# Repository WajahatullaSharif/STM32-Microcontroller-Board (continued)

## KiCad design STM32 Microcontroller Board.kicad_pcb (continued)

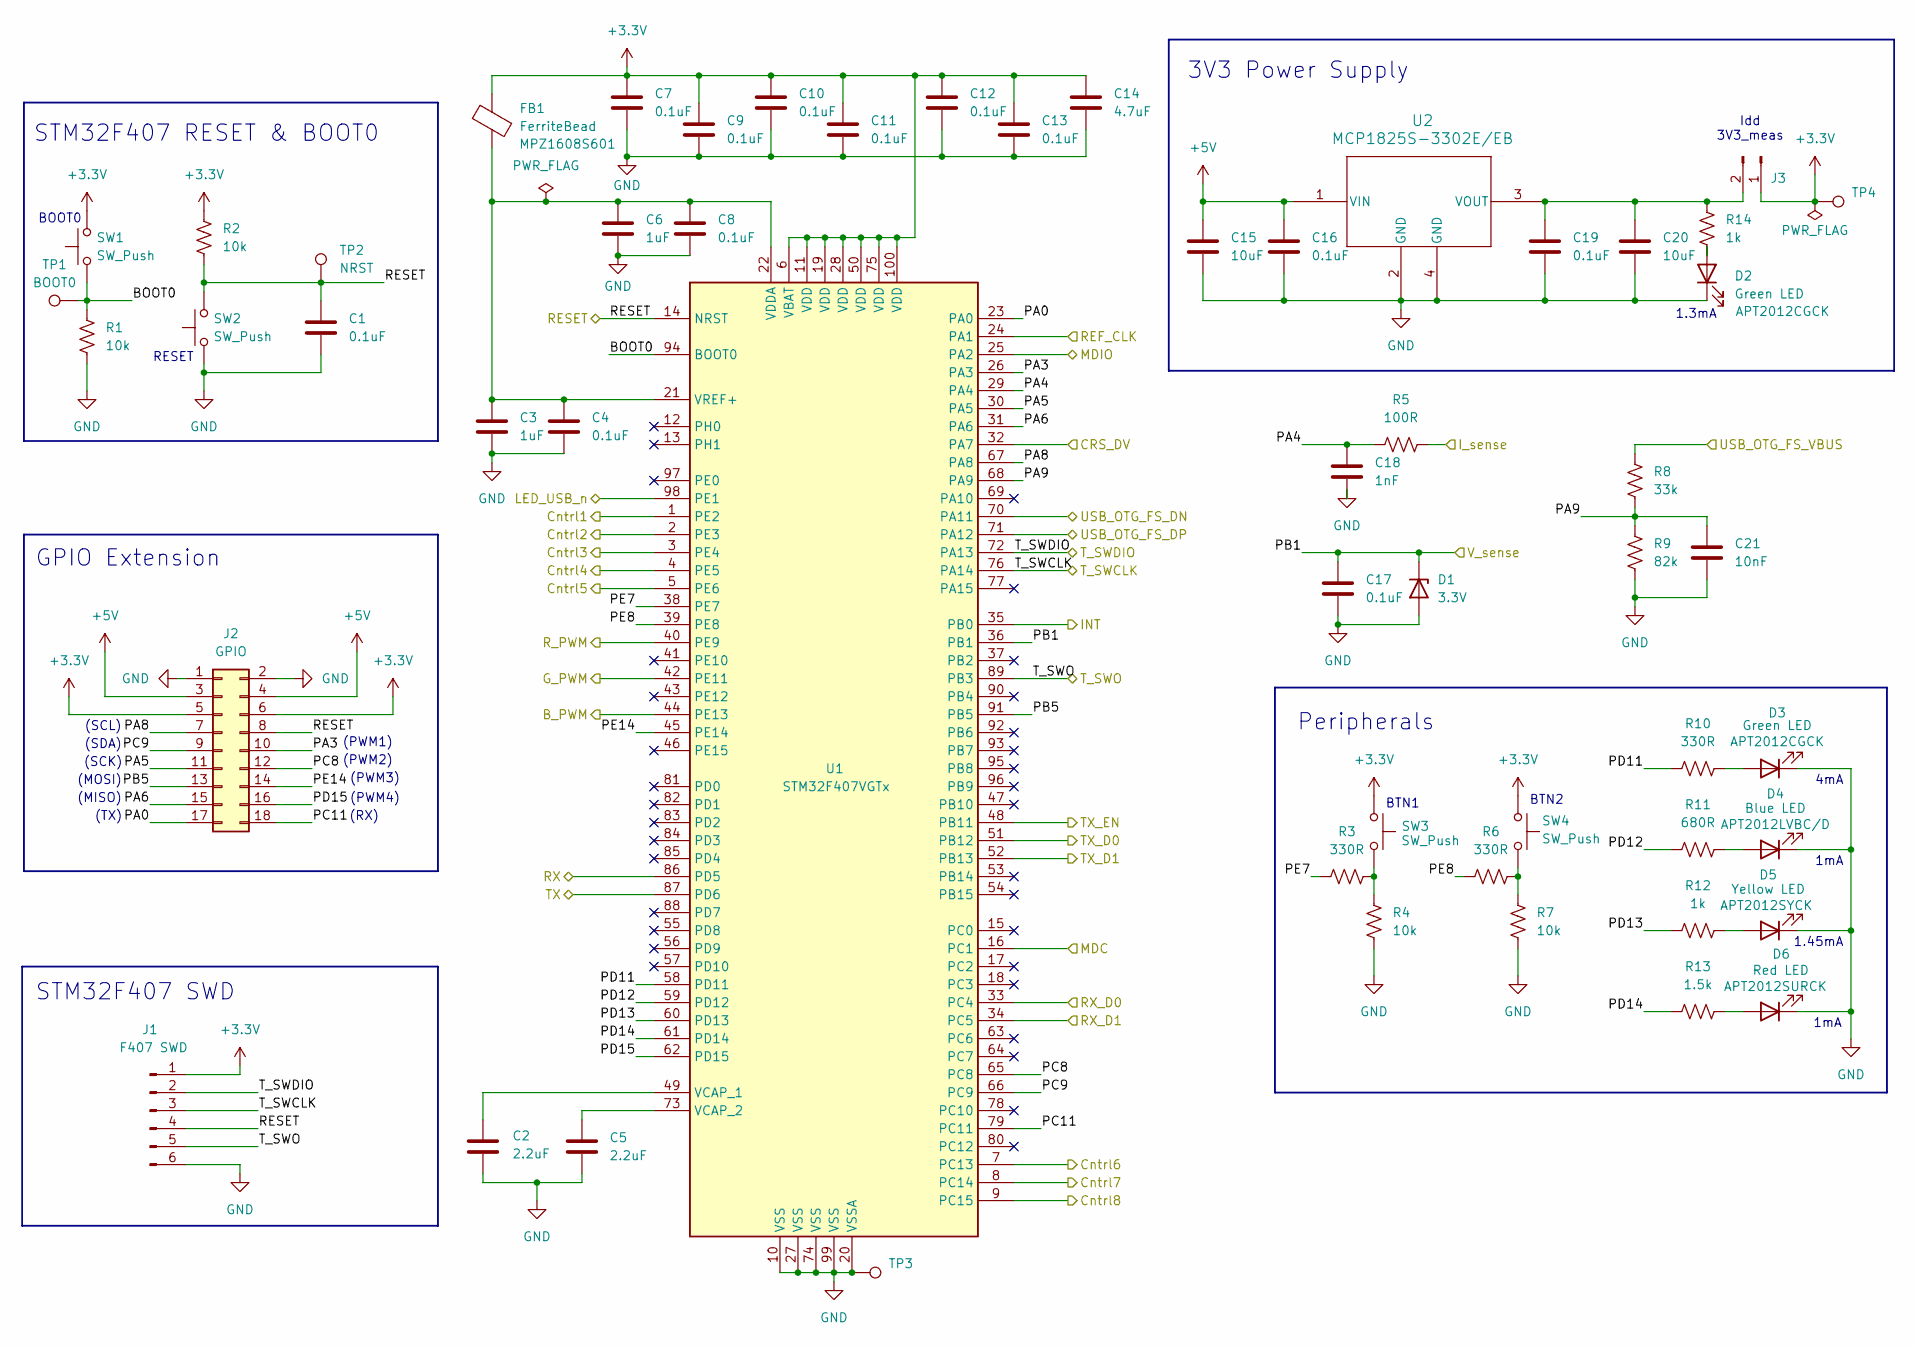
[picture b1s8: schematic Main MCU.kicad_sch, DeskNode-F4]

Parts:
C1, C4, C7, C8, C9, C10, C11, C12, C13, C16, C17, C19: 0.1uF; C_0402_1005Metric; MPN GRM155R71A104KA01D
C2, C5: 2.2uF; C_0603_1608Metric; MPN CL10B225KP8NNNC
C3, C6: 1uF; C_0603_1608Metric; MPN CL10B105KP8NNNC
C14: 4.7uF; C_0805_2012Metric; MPN GRM21BR71C475KE51L
C15, C20: 10uF; C_0805_2012Metric; MPN CL21B106KOQNNNE
C18: 1nF; C_0603_1608Metric; MPN C0603C102K4RACTU
C21: 10nF; C_0402_1005Metric; MPN GRM155R71E103KA01D
D1: 3.3V; D_SOD-323F; MPN MM3Z3V3T1G
D2, D3: Green LED; LED_0805_2012Metric; MPN APT2012CGCK
D4: Blue LED; LED_0805_2012Metric; MPN APT2012LVBC/D
D5: Yellow LED; LED_0805_2012Metric; MPN APT2012SYCK
D6: Red LED; LED_0805_2012Metric; MPN APT2012SURCK
FB1: FerriteBead; L_0603_1608Metric; MPN MPZ1608S601ATA00
J1: F407 SWD; PinHeader_1x06_P2.54mm_Vertical
J2: GPIO; PinHeader_2x09_P2.54mm_Vertical
J3: Conn_01x02_Pin; PinHeader_1x02_P2.54mm_Vertical
R1, R2, R4, R7: 10k; R_0603_1608Metric; MPN RC0603FR-0710KL
R3, R6, R10: 330R; R_0603_1608Metric; MPN RC0603FR-07330RL
R5: 100R; R_0603_1608Metric; MPN RC0603FR-07100RL
R8: 33k; R_0603_1608Metric; MPN RC0603FR-0733KL
R9: 82k; R_0603_1608Metric; MPN RC0603FR-0782KL
R11: 680R; R_0603_1608Metric; MPN RC0603FR-07680RL
R12, R14: 1k; R_0603_1608Metric; MPN RC0603FR-071KL
R13: 1.5k; R_0603_1608Metric; MPN RC0603FR-071K5L
SW1, SW2, SW3, SW4: SW_Push; SW_SPST_PTS645Sx43SMTR92; MPN SWT0310-043016GSA
TP1: BOOT0; TestPoint_Pad_D1.0mm
TP2: NRST; TestPoint_Pad_D1.0mm
TP3, TP4: TestPoint; TestPoint_Keystone_5000-5004_Miniature; MPN 5001
U1: STM32F407VGTx; LQFP-100_14x14mm_P0.5mm; MPN STM32F407VGT6
U2: MCP1825S-3302E/EB; DDPAK3_MC_MCH-L; MPN MCP1825S-3302E/EB

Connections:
+3.3V: C7.1, C9.1, C10.1, C11.1, C12.1, C13.1, C14.1, FB1.2, J1.1, J2.5, J2.6, J3.1, R2.1, SW1.2, SW3.1, SW4.1, TP4.1, U1.6 (VBAT), U1.11 (VDD), U1.19 (VDD), U1.28 (VDD), U1.50 (VDD), U1.75 (VDD), U1.100 (VDD); also elsewhere on the board
+5V: C15.1, C16.1, J2.3, J2.4, U2.1 (VIN); also elsewhere on the board
/AC PWR ctrl & USB FS/Cntrl1: U1.1 (PE2); also elsewhere on the board
/AC PWR ctrl & USB FS/Cntrl2: U1.2 (PE3); also elsewhere on the board
/AC PWR ctrl & USB FS/Cntrl3: U1.3 (PE4); also elsewhere on the board
/AC PWR ctrl & USB FS/Cntrl4: U1.4 (PE5); also elsewhere on the board
/AC PWR ctrl & USB FS/Cntrl5: U1.5 (PE6); also elsewhere on the board
/AC PWR ctrl & USB FS/Cntrl6: U1.7 (PC13); also elsewhere on the board
/AC PWR ctrl & USB FS/Cntrl7: U1.8 (PC14); also elsewhere on the board
/AC PWR ctrl & USB FS/Cntrl8: U1.9 (PC15); also elsewhere on the board
/AC PWR ctrl & USB FS/LED_USB_n: U1.98 (PE1); also elsewhere on the board
/AC PWR ctrl & USB FS/USB_OTG_FS_DN: U1.70 (PA11); also elsewhere on the board
/AC PWR ctrl & USB FS/USB_OTG_FS_DP: U1.71 (PA12); also elsewhere on the board
/AC PWR ctrl & USB FS/USB_OTG_FS_VBUS: R8.1; also elsewhere on the board
/Debugger/RX: U1.87 (PD6); also elsewhere on the board
/Debugger/TX: U1.86 (PD5); also elsewhere on the board
/Ethernet PHY/CRS_DV: U1.32 (PA7); also elsewhere on the board
/Ethernet PHY/INT: U1.35 (PB0); also elsewhere on the board
/Ethernet PHY/MDC: U1.16 (PC1); also elsewhere on the board
/Ethernet PHY/MDIO: U1.25 (PA2); also elsewhere on the board
/Ethernet PHY/REF_CLK: U1.24 (PA1); also elsewhere on the board
/Ethernet PHY/RX_D0: U1.33 (PC4); also elsewhere on the board
/Ethernet PHY/RX_D1: U1.34 (PC5); also elsewhere on the board
/Ethernet PHY/TX_D0: U1.51 (PB12); also elsewhere on the board
/Ethernet PHY/TX_D1: U1.52 (PB13); also elsewhere on the board
/Ethernet PHY/TX_EN: U1.48 (PB11); also elsewhere on the board
/LED Driver/B_PWM: U1.44 (PE13); also elsewhere on the board
/LED Driver/G_PWM: U1.42 (PE11); also elsewhere on the board
/LED Driver/I_sense: R5.2; also elsewhere on the board
/LED Driver/R_PWM: U1.40 (PE9); also elsewhere on the board
/Main MCU/BOOT0: R1.1, SW1.1, TP1.1, U1.94 (BOOT0)
/Main MCU/PA0: J2.17, U1.23 (PA0)
/Main MCU/PA3: J2.10, U1.26 (PA3)
/Main MCU/PA4: C18.1, R5.1, U1.29 (PA4)
/Main MCU/PA5: J2.11, U1.30 (PA5)
/Main MCU/PA6: J2.15, U1.31 (PA6)
/Main MCU/PA8: J2.7, U1.67 (PA8)
/Main MCU/PA9: C21.1, R8.2, R9.1, U1.68 (PA9)
/Main MCU/PB1: C17.1, D1.1 (K), U1.36 (PB1); also elsewhere on the board
/Main MCU/PB5: J2.13, U1.91 (PB5)
/Main MCU/PC8: J2.12, U1.65 (PC8)
/Main MCU/PC9: J2.9, U1.66 (PC9)
/Main MCU/PC11: J2.18, U1.79 (PC11)
/Main MCU/PD11: R10.1, U1.58 (PD11)
/Main MCU/PD12: R11.1, U1.59 (PD12)
/Main MCU/PD13: R12.1, U1.60 (PD13)
/Main MCU/PD14: R13.1, U1.61 (PD14)
/Main MCU/PD15: J2.16, U1.62 (PD15)
/Main MCU/PE7: R3.1, U1.38 (PE7)
/Main MCU/PE8: R6.1, U1.39 (PE8)
/Main MCU/PE14: J2.14, U1.45 (PE14)
/Main MCU/RESET: C1.1, J1.4, J2.8, R2.2, SW2.2, TP2.1, U1.14 (NRST); also elsewhere on the board
/Main MCU/T_SWCLK: J1.3, U1.76 (PA14); also elsewhere on the board
/Main MCU/T_SWDIO: J1.2, U1.72 (PA13); also elsewhere on the board
/Main MCU/T_SWO: J1.5, U1.89 (PB3); also elsewhere on the board
GND: C1.2, C2.2, C3.2, C4.2, C5.2, C6.2, C7.2, C8.2, C9.2, C10.2, C11.2, C12.2, C13.2, C14.2, C15.2, C16.2, C17.2, C18.2, C19.2, C20.2, C21.2, D1.2 (A), D2.1 (K), D3.1 (K), D4.1 (K), D5.1 (K), D6.1 (K), J1.6, J2.1, J2.2, R1.2, R4.2, R7.2, R9.2, SW2.1, TP3.1, U1.10 (VSS), U1.20 (VSSA), U1.27 (VSS), U1.74 (VSS), U1.99 (VSS), U2.2 (GND), U2.4 (GND); also elsewhere on the board
unnamed: D2.2 (A), R14.2
unnamed: D3.2 (A), R10.2
unnamed: D4.2 (A), R11.2
unnamed: D5.2 (A), R12.2
unnamed: D6.2 (A), R13.2
unnamed: C19.1, C20.1, J3.2, R14.1, U2.3 (VOUT)
unnamed: R3.2, R4.1, SW3.2
unnamed: R6.2, R7.1, SW4.2
unnamed: C2.1, U1.49 (VCAP_1)
unnamed: C5.1, U1.73 (VCAP_2)
unnamed: C3.1, C4.1, C6.1, C8.1, FB1.1, U1.21 (VREF+), U1.22 (VDDA)

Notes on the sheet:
(SCL)
(PWM3)
1mA
(RX)
BTN1
(MISO)
STM32F407 RESET & BOOT0
BOOT0
(TX)
STM32F407 SWD
(PWM2)
1.45mA
Idd 3V3_meas
3V3 Power Supply
4mA
1.3mA
(PWM1)
(PWM4)
RESET
(SDA)
(SCK)
GPIO Extension
(MOSI)
Peripherals
BTN2

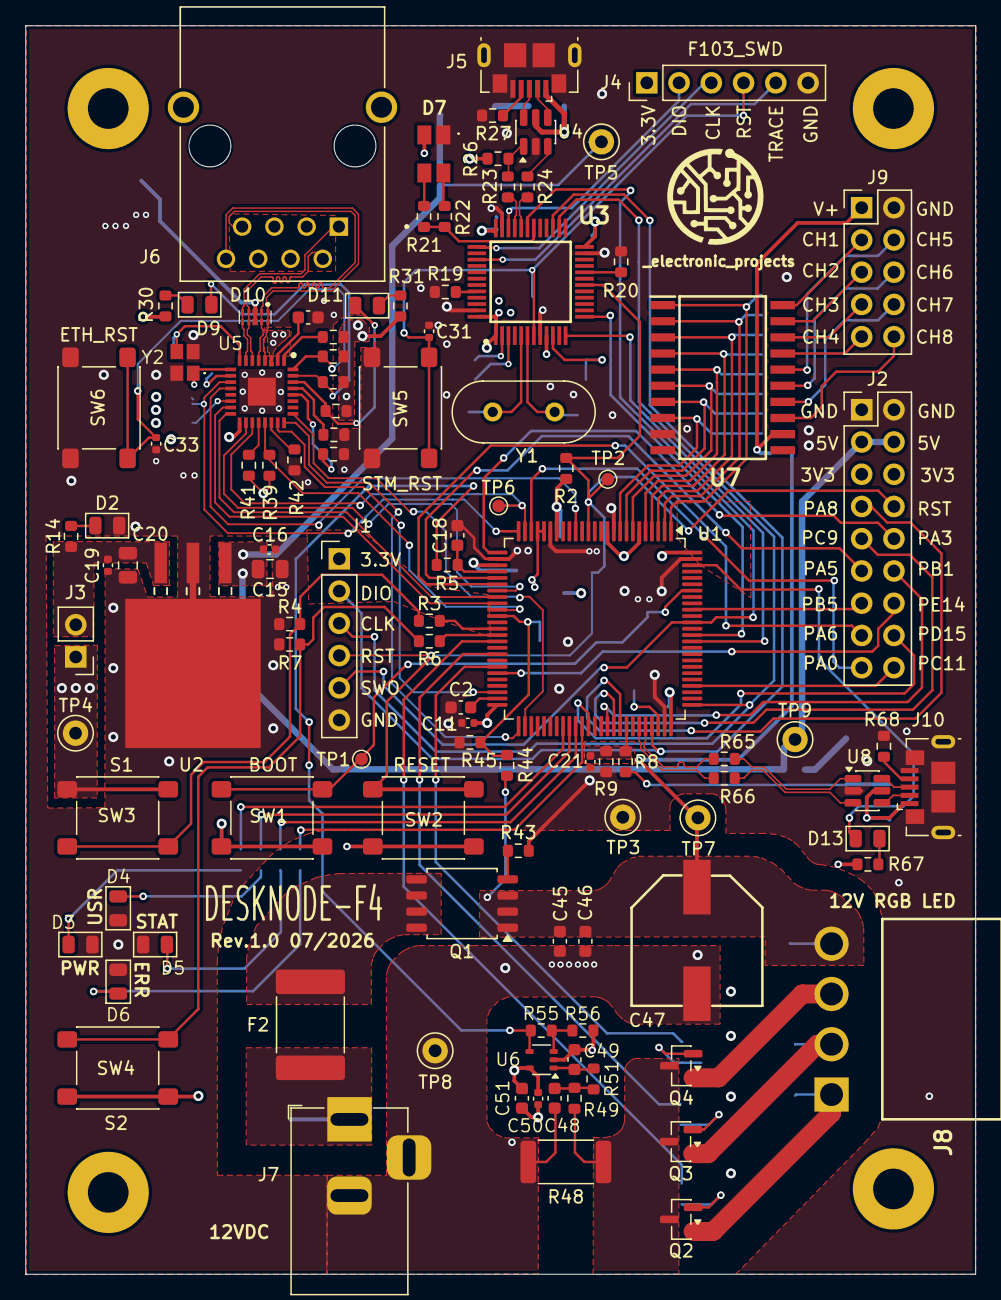
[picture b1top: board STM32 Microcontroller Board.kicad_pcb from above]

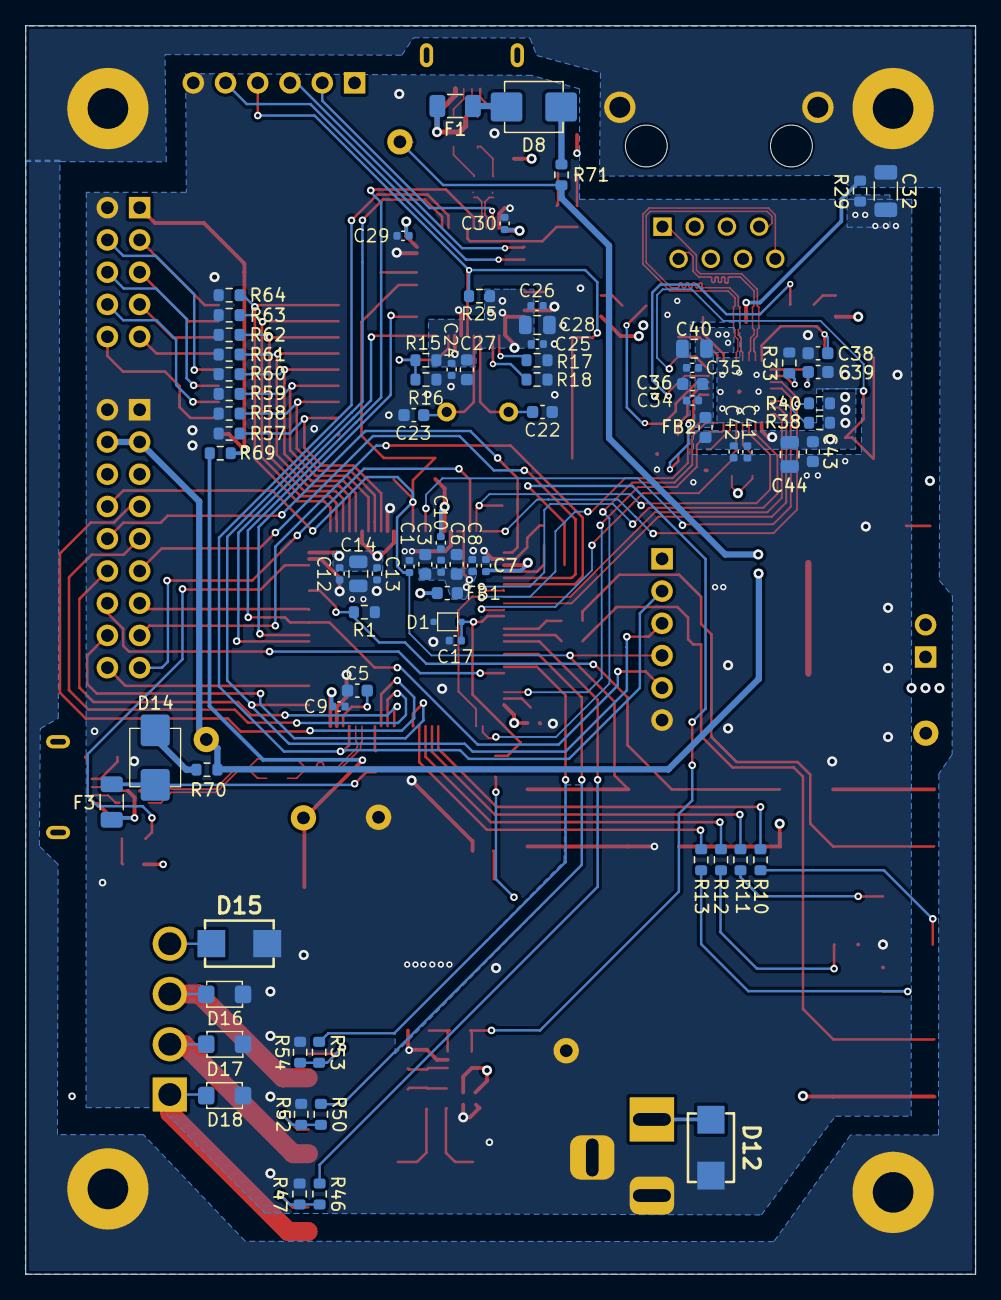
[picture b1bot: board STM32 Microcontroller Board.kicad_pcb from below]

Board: 4 copper layers, 74.8 x 98.3 mm, 188 parts (76 on the bottom side), 143 nets.

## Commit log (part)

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2026-04-16 Initial commit of KiCad project
2026-04-16 Apply .gitignore and remove backup files
2026-05-11 Your descriptive message here
2026-05-13 Added 3V3 Power Supply
2026-05-14 MCU power supplied
2026-05-15 Added user buttons and boot config
2026-05-21 Updated the root schematic page
2026-05-24 Done ERC + Documentation
2026-05-31 Initial Review Changes
2026-06-08 MPNs updated
2026-06-11 Layout placement
2026-06-23 Layout Routing
2026-06-24 Layout - 12V Power path
2026-06-24 Updated layout
2026-06-25 12V i/p FIlter caps removed
2026-06-27 Layout complete with DRC resolution
2026-06-28 Review files
